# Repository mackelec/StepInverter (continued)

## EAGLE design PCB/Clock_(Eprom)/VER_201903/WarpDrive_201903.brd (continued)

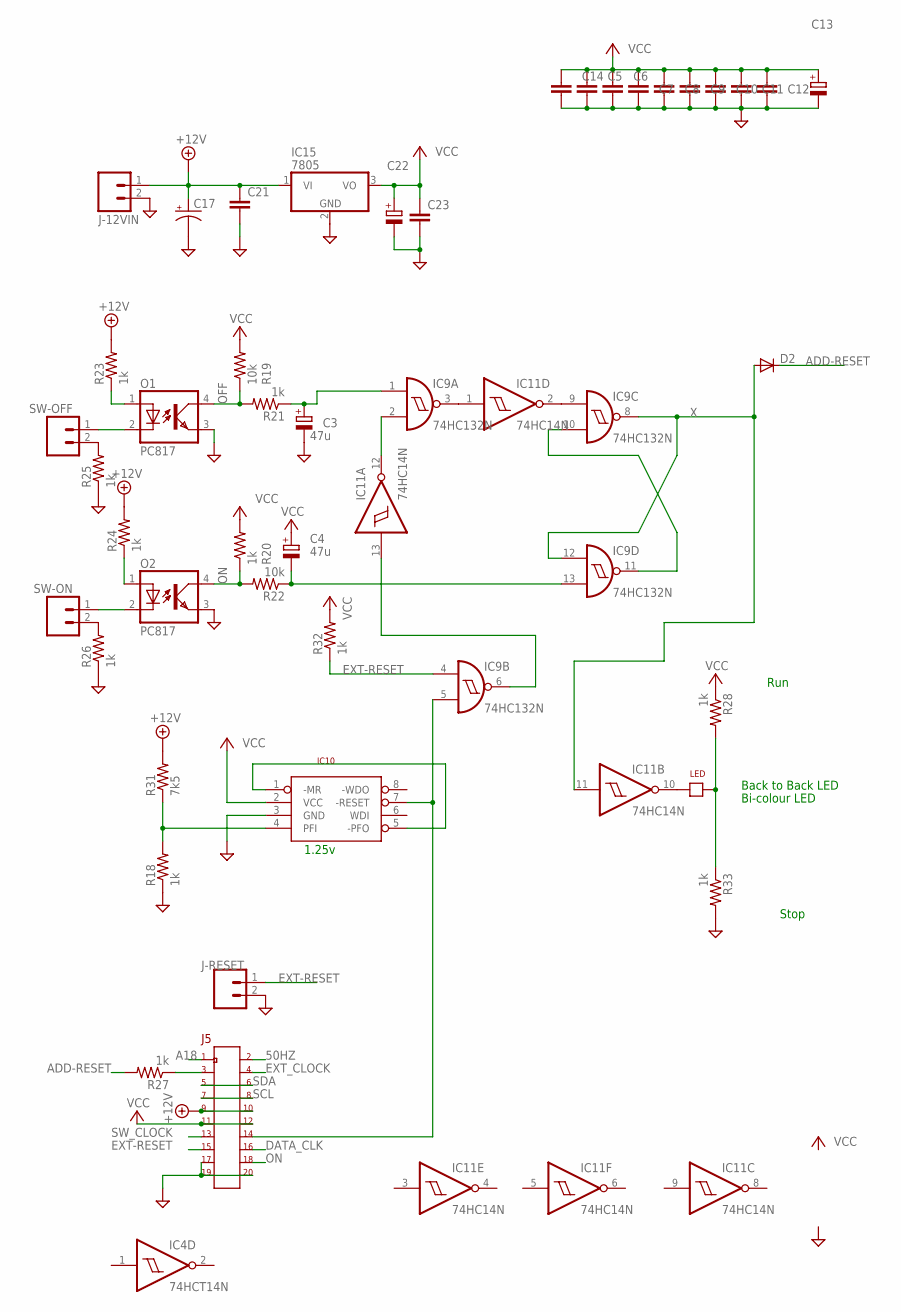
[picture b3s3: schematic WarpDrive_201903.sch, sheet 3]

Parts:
C3, C4: 47u; CPOL-RADIAL-10UF-25V
C5, C6, C7, C8, C9, C10, C11, C12, C14, C21, C23: BCAP
C13, C22: C-RB200100; CPOL-RADIAL-10UF-25V
C17: CAP_POLPTH1; CPOL-RADIAL-100UF-25V
D2: 1N4148DO35-7; D3
IC4: 74HCT14N; DIL14
IC9: 74HC132N; DIL14
IC10: ADM705; DIL08
IC11: 74HC14N; DIL14
IC15: 7805; TO220V
J5: IDC20IDC20-SMALL; IDC20-SMALL
J-12VIN: MO2POL; MOLEX-1X2
J-RESET: MO2POL; MOLEX-1X2
LED: JP1
O1, O2: PC817; DIL04
R18, R20, R21, R23, R24, R25, R26, R27, R28, R32, R33: 1k; AXIAL-0.4
R19, R22: 10k; AXIAL-0.4
R31: 7k5; AXIAL-0.4
SW-OFF: MO2POL; MOLEX-1X2
SW-ON: MO2POL; MOLEX-1X2

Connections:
50HZ: J5.2; also elsewhere on the board
+12V: C17.1 (+), C21.1, IC15.1 (VI), J5.9, J5.10, J-12VIN.1, R23.P$2 (2), R24.P$2 (2), R31.P$2 (2)
A18: J5.1; also elsewhere on the board
ADD-RESET: D2.C, R27.P$2 (2); also elsewhere on the board
DATA_CLK: J5.16; also elsewhere on the board
EXT-RESET: IC9.4 (I0), J5.15, J-RESET.1, R32.P$1 (1)
EXT_CLOCK: J5.4; also elsewhere on the board
GND: C3.2 (-), C5.2, C6.2, C7.2, C8.2, C9.2, C10.2, C11.2, C12.2, C13.2 (-), C14.2, C17.2 (-), C21.2, C22.2 (-), C23.2, IC4.7 (GND), IC9.7 (GND), IC10.3 (GND), IC11.7 (GND), IC15.2 (GND), J5.17, J5.19, J5.20, J-12VIN.2, J-RESET.2, O1.3 (EMIT), O2.3 (EMIT), R18.P$1 (1), R25.P$1 (1), R26.P$1 (1), R33.P$2 (2); also elsewhere on the board
unnamed: IC9.9 (I0), IC11.2 (O)
unnamed: LED.2, R28.P$2 (2), R33.P$1 (1)
unnamed: R25.P$2 (2), SW-OFF.2
unnamed: J5.3, R27.P$1 (1)
unnamed: R26.P$2 (2), SW-ON.2
unnamed: IC9.10 (I1), IC9.11 (O)
unnamed: C3.1 (+), IC9.1 (I0), R21.P$1 (1)
unnamed: IC9.3 (O), IC11.1 (I)
unnamed: C4.2 (-), IC9.13 (I1), R22.P$1 (1)
unnamed: O1.1 (A), R23.P$1 (1)
unnamed: O1.2 (C), SW-OFF.1
unnamed: O2.1 (A), R24.P$1 (1)
unnamed: O2.2 (C), SW-ON.1
unnamed: IC9.2 (I1), IC11.12 (O)
unnamed: IC9.6 (O), IC11.13 (I)
unnamed: IC9.5 (I1), IC10.7 (-RESET), J5.14
unnamed: IC10.1 (-MR), IC10.5 (-PFO)
unnamed: IC10.4 (PFI), R18.P$2 (2), R31.P$1 (1)
unnamed: IC11.10 (O), LED.1
OFF: O1.4 (COL), R19.P$1 (1), R21.P$2 (2)
ON: J5.18, O2.4 (COL), R20.P$1 (1), R22.P$2 (2)
SCL: J5.7, J5.8; also elsewhere on the board
SDA: J5.5, J5.6; also elsewhere on the board
SW_CLOCK: J5.13; also elsewhere on the board
VCC: C4.1 (+), C5.1, C6.1, C7.1, C8.1, C9.1, C10.1, C11.1, C12.1, C13.1 (+), C14.1, C22.1 (+), C23.1, IC4.14 (VCC), IC9.14 (VCC), IC10.2 (VCC), IC11.14 (VCC), IC15.3 (VO), J5.11, J5.12, R19.P$2 (2), R20.P$2 (2), R28.P$1 (1), R32.P$2 (2); also elsewhere on the board
X: D2.A, IC9.8 (O), IC9.12 (I0), IC11.11 (I)

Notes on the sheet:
1.25v
Run
Stop
Back to Back LED
Bi-colour LED

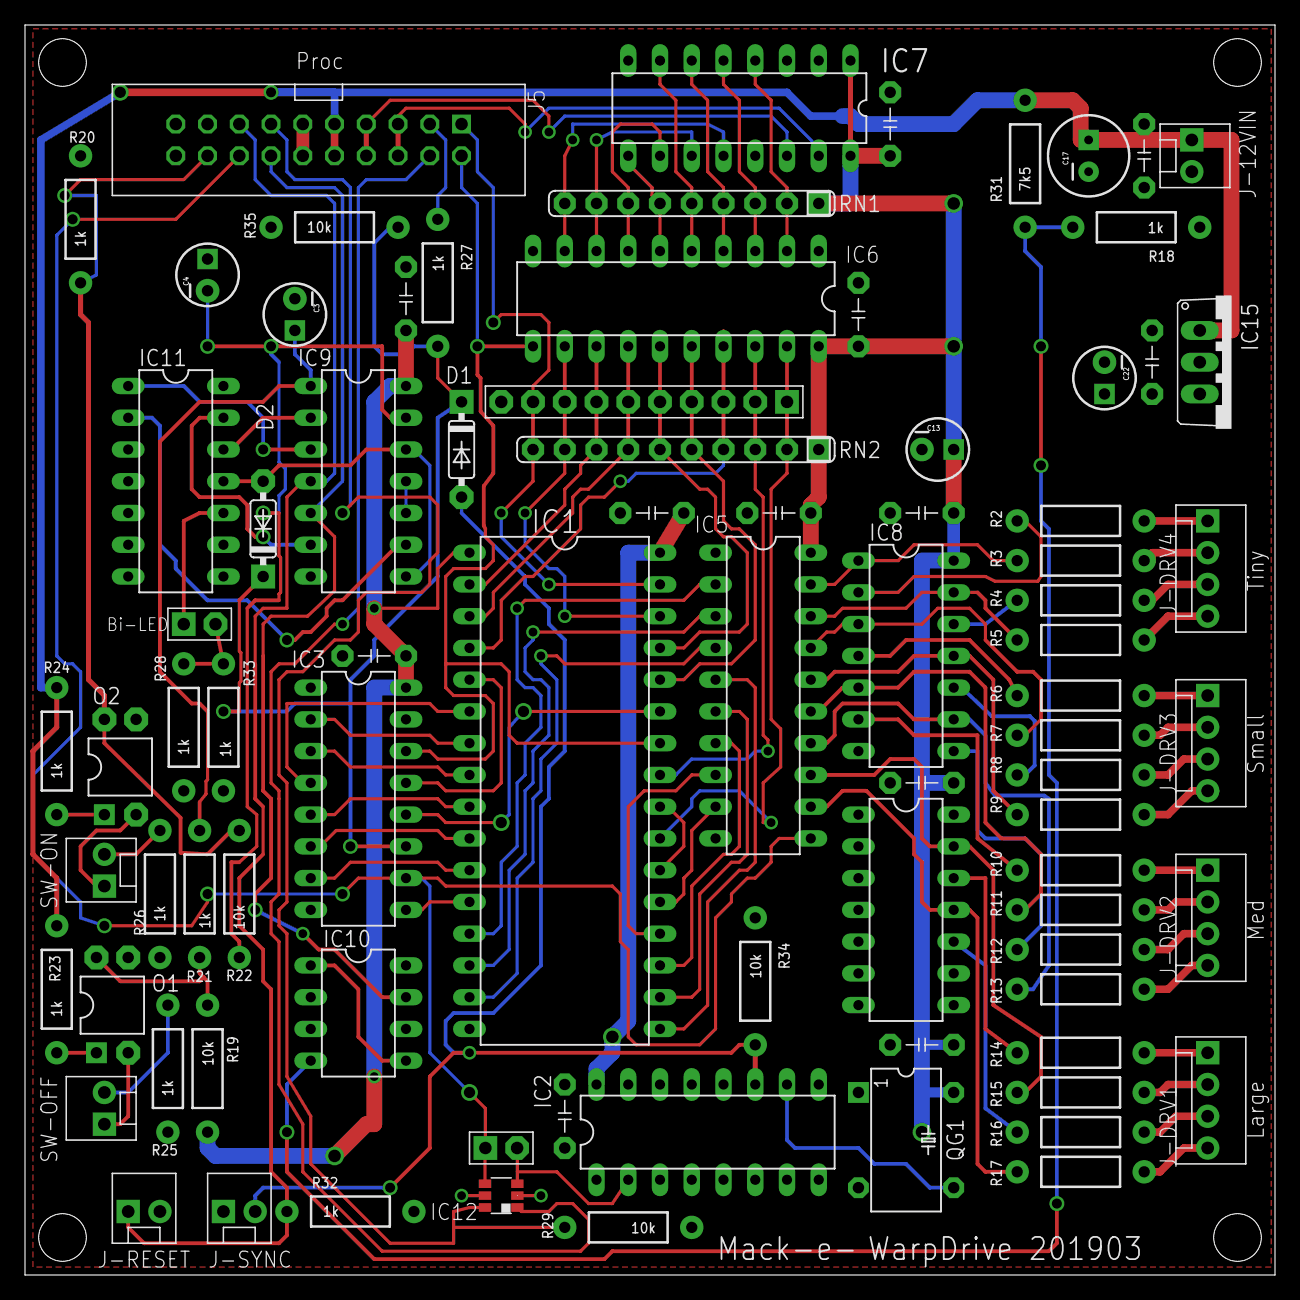
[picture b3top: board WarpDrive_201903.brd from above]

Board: 2 copper layers, 100.0 x 100.0 mm, 83 parts (0 on the bottom side), 102 nets.

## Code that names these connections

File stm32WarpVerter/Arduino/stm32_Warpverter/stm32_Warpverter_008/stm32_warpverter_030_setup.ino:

void setup() 
{
  afio_cfg_debug_ports(AFIO_DEBUG_NONE);
  Serial.begin(9600);
  while (!Serial) 
   {
    ; // wait for serial port to connect. Needed for native USB port only
   }
  pinMode(pin50Hz,OUTPUT);
  pinMode(PB3,OUTPUT);      // test pin  : toggles on timer
  pinMode(PB5,OUTPUT);      // test pin
  pinMode(PB4,OUTPUT);      // test pin 
  pinMode(PA15,OUTPUT);      // test pin 

  pinMode(adcPinI,INPUT_ANALOG);
  pinMode(PIN_THERM1,INPUT_ANALOG);
  pinMode(PIN_THERM2,INPUT_ANALOG);
  pinMode(PIN_VAC,INPUT_ANALOG);
  pinMode(PIN_IAC,INPUT_ANALOG);
  
  
//  pinMode(PA4,OUTPUT);
//  pinMode(PC14,OUTPUT);
//  pinMode(PC15,OUTPUT);
//  pinMode(PB7,OUTPUT);
//  pinMode(PA15,OUTPUT);
  pinMode(LED,OUTPUT);
  //slow way
  pinMode(PB8,OUTPUT);
  pinMode(PB9,OUTPUT);
  pinMode(PB10,OUTPUT);
  pinMode(PB11,OUTPUT);
  pinMode(PB12,OUTPUT);
  pinMode(PB13,OUTPUT);
  pinMode(PB14,OUTPUT);
  pinMode(PB15,OUTPUT);

  pinMode(pinSwOff,INPUT_PULLUP);
  pinMode(pinSwON,INPUT_PULLUP);
  pinMode(PIN_SYNCINP,INPUT_PULLUP);

  pinMode(pinFAN1,PWM);
  pinMode(pinFAN2,PWM);
  pinMode(pinRelay,OUTPUT);

  bool tablesCheck = checkTables();
  
  //---   BluePill onboard LED is turned by writing LOW 
  //        opposite of most arduino boards  
  digitalWrite(LED,LOW);
  delay(1000);
  Serial.flush();
  // quick way, the upper 8 bits all set to output, pushpull
  GPIOB->regs->CRH = 0x33333333;
  GPIOB->regs->ODR = 0;

  

/*-----------------------------------------------
 *  
 *      ADC setup
 *      
 *      -  STM32F103 has dual ADCs 
 *           ADC2 reads Battery Voltage
 *           ADC1 is used in scan mode, multiplexed, 
 *             reads Thermistor 1 & 2, Battery Current, AC voltage and Current 
 *      -  ADC 1 & 2 are set in continuous conversion modeso we don't waste time servicing it.
 *      -  ADC1 is using DMA into a 5 element buffer.
 *      -  Using the the same scan rate as in the powerScope so it is faster than 6400Hz
 *      
 *  
 ------------------------------------------------*/

  adcV.calibrate();
  adcV.setSampleRate(ADC_SMPR_239_5);
  adcV.setPins(&adcPinV, 1);
  adcV.setContinuous();

  adc_2.calibrate();
  adc_2.setSampleRate(ADC_SMPR_239_5);//set the Sample Rate
  adc_2.setScanMode();              
  adc_2.setPins(analogInputs, 5);   //set how many and which pins to convert.
  adc_2.setContinuous();            //set the ADC in continuous mode.

//set the DMA transfer for the ADC. 
//in this case we want to increment the memory side and run it in circular mode
//By doing this, we can read the last value sampled from the channels by reading the dataPoints array
  adc_2.setDMA(adcData, 5, (DMA_MINC_MODE | DMA_CIRC_MODE), NULL);

  adcV.startConversion();
  adc_2.startConversion();
  
  
  //*******  Timer setup  ( 19.52777777777777777778 microseconds, 51209.10384068278805121 Hz)
  //---  output Frquency = 50.00889046941678520626 Hz
  //---  inverterTimer frequency = 51200Hz (50Hz x 1024 steps)
  //---  inverterTimer period = 19.53125 uSec
  //---  overflow = 72MHz / 51200Hz = 1406.25
  
  inverterTimer.setMode(TIMER_CH4, TIMER_OUTPUT_COMPARE);
  inverterTimer.pause();
  inverterTimer.setPrescaleFactor(1);//1
  inverterTimer.setCount(0);
  inverterTimer.setOverflow(TIMER_OVERFLOW);//1406
  inverterTimer.setCompare(TIMER_CH4, 1);  
  inverterTimer.attachCompare4Interrupt(timer_Handler);
  inverterTimer.refresh();
  
  delay(1000);
  Serial << "stm32-StepInverter  Setup done" << endl;
  Serial.flush();

   //--- Starting with Inverter running for testing purposes.
   //---   I prefer Inverter NOT  running on start-up in real use.
  inverterRunning = true;    // 
  //digitalWrite(LED,HIGH);  // uncomment if startup with inverter off


  // mains sync
  p_lock = 0;          // phase lock flag = 0 = NOT locked
  pcount_acc = 0;      // fractional integer math. Each PWM, pcount_delta is added to pcount_acc and divided by 1024
  pcount_delta = 1024; // in effect we are getting an addition of 1. But pcount_delta can be modified, a little bigger or smaller..
  old_phase_error = 0; // used in PID, to obtain derivative
  int_f = 0;            // flag used to allow one and only one interrupt, near a zero crossing of AC output
  p_lock = 0;           // use this to tell if phase lock is present or not
  attachInterrupt(PA1,mains_sync,FALLING);
  
  inverterTimer.resume();

}


/*------------------------------------------------------------
 * 
 *      CheckTables : Checks the size of the in - flash arrays
 *      
 *                    -  View the report on Serial Monitor
 *                       after pasting the array data.
 * 
 ------------------------------------------------------------*/

bool checkTables()
{
  int Vsize = sizeof(flash_voltMaskTable);
  int sineSize = sizeof(flash_sineLookup)/2;
  int sizeIF = sizeof(flash_inputFactorTable);
  bool result = true;
  Serial << endl;
  Serial.flush();
  while (!Serial) 
   {
    ; // wait for serial port to connect. Needed for native USB port only
   }
   delay(1000);
   Serial << "voltMaskTable size = " << Vsize;
   if (Vsize == 0x2000) {Serial << " -- Good " << endl; } else {Serial << "  -- Fail" << endl;result = false;}
   Serial.flush();
   Serial << "sineLookup size = " << sineSize;
   if (sineSize == STEPS) {Serial << " -- Good " << endl; } else {Serial << "  -- Fail" << endl;result = false;}
   Serial.flush();
   Serial << "inputFactorTable size = " << sizeIF;
   if (sizeIF == 0x2000) {Serial << " -- Good " << endl; } else {Serial << "  -- Fail" << endl;result = false;}
   Serial.flush();
   delay(1000);
   return (result);
   
}

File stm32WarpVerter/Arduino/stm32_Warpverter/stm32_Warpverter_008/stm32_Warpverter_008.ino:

#include <Streaming.h>
#include <PString.h>
#include <STM32ADC.h>

STM32ADC adcV(ADC2);
STM32ADC adc_2(ADC1);

uint8 adcPinV = PB0;
uint8 adcPinI = PB1;

#define PIN_SYNCINP PA1
#define pinSwOff    PC15
#define pinSwON     PC14
#define pinFAN1     PA3
#define pinFAN2     PA2
#define pinRelay    PA8

#define setRelay gpio_write_bit(GPIOA, 8, HIGH)
#define clrRelay gpio_write_bit(GPIOA, 8, LOW)

#define setFAN1 gpio_write_bit(GPIOA, 3, HIGH)
#define clrFAN1 gpio_write_bit(GPIOA, 3, LOW)

#define setFAN2 gpio_write_bit(GPIOA, 2, HIGH)
#define clrFAN2 gpio_write_bit(GPIOA, 2, LOW)

#define pin50Hz PA0
#define set50Hz gpio_write_bit(GPIOA, 0, LOW)
#define clr50Hz gpio_write_bit(GPIOA, 0, HIGH)

#define clrPB5 gpio_write_bit(GPIOB, 5, LOW)
#define setPB5 gpio_write_bit(GPIOB, 5, HIGH)

#define clrPB4 gpio_write_bit(GPIOB, 4, LOW)
#define setPB4 gpio_write_bit(GPIOB, 4, HIGH)

#define clrPA15 gpio_write_bit(GPIOA, 15, LOW)
#define setPA15 gpio_write_bit(GPIOA, 15, HIGH)

volatile uint16 adcValueV;
volatile uint16 adcValueI;

volatile int32 avgADC_V;
//volatile int32 avgADC_I;

byte  outputDrive = 0;    // Output Driver : High Byte of PORT B 
uint16 cycleIndex;           // position within the cycle : between 0 to 1023 , 
int32 inputFactor = 10000;

bool inverterRunning = false;
int16 onPressed;
bool fan1ON = false;
bool fan2ON = false;

HardwareTimer inverterTimer(3);//4

#define PIN_THERM1 PA5
#define PIN_THERM2 PA4
#define PIN_VAC    PA7
#define PIN_IAC    PA6



uint8 analogInputs[] = {PIN_THERM1,PIN_THERM2,adcPinI,PIN_VAC,PIN_IAC};
uint16_t adcData[5];

#define STEPS 1024
#define VOLTSTEPS   int(pow(3,TRANSFORMER_COUNT))
#define VOLT_MASK_TABLE flash_voltMaskTable
#define SINE_LOOKUP_TABLE flash_sineLookup

#define adcTherm1  adcData[0]
#define adcTherm2  adcData[1]
#define avgADC_I   adcData[2]

char message[256];
PString pMessage(message,sizeof(message));

#define LED      PC13


//
// mains sync
//
long pcount_acc;
int pcount_delta, phase_error, old_phase_error;
int int_f,p_lock;






void loop() {
  // put your main code here, to run repeatedly:

}

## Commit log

2019-03-09 Create junk
